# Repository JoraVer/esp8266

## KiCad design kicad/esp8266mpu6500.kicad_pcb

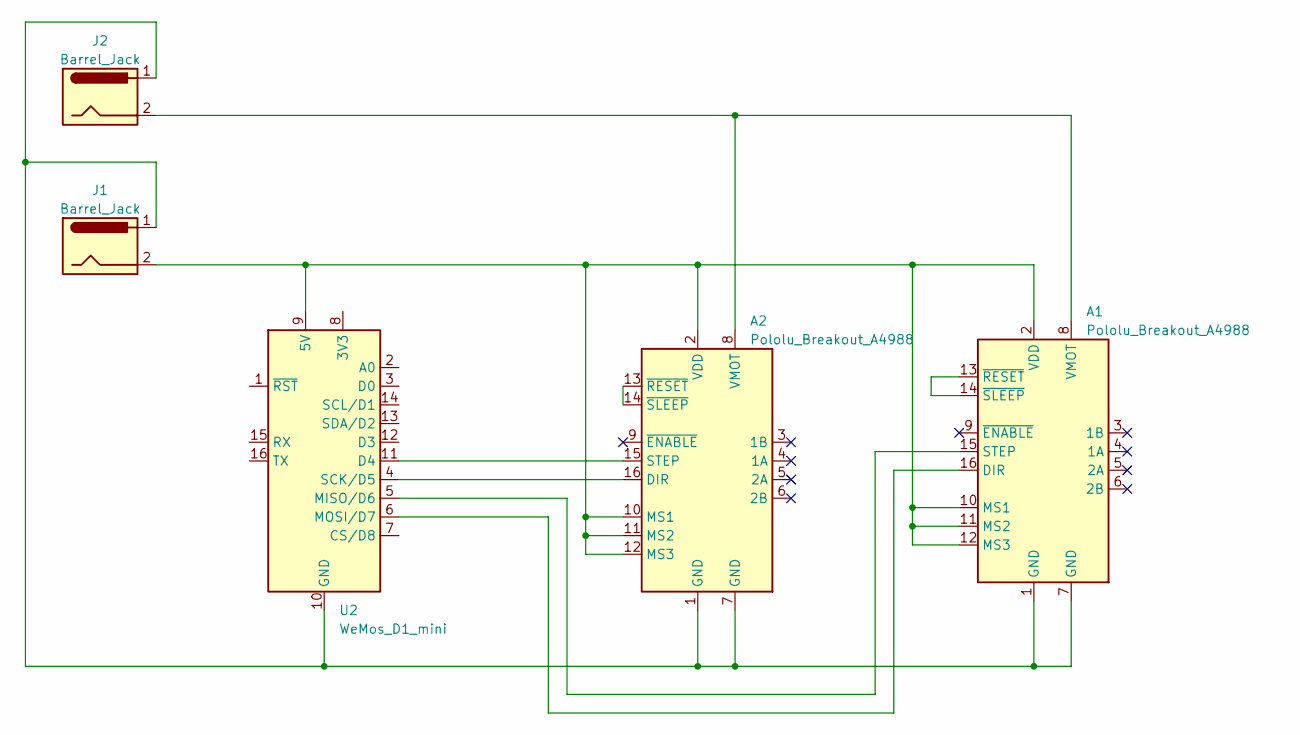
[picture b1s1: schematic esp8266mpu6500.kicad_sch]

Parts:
A1, A2: Pololu_Breakout_A4988; Pololu_Breakout-16_15.2x20.3mm
J1, J2: Barrel_Jack; BarrelJack_SwitchcraftConxall_RAPC10U_Horizontal
U2: WeMos_D1_mini; WEMOS_D1_mini_light

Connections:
unnamed: A1.16 (DIR), U2.6 (MOSI/D7)
unnamed: A1.2 (VDD), A1.10 (MS1), A1.11 (MS2), A1.12 (MS3), A2.2 (VDD), A2.10 (MS1), A2.11 (MS2), A2.12 (MS3), J1.2, U2.9 (5V)
unnamed: A1.15 (STEP), U2.5 (MISO/D6)
unnamed: A1.8 (VMOT), A2.8 (VMOT), J2.2
unnamed: A1.13 (~RESET), A1.14 (~SLEEP)
unnamed: A2.16 (DIR), U2.4 (SCK/D5)
unnamed: A2.15 (STEP), U2.11 (D4)
unnamed: A2.13 (~RESET), A2.14 (~SLEEP)
unnamed: A1.1 (GND), A1.7 (GND), A2.1 (GND), A2.7 (GND), J1.1, J2.1, U2.10 (GND)

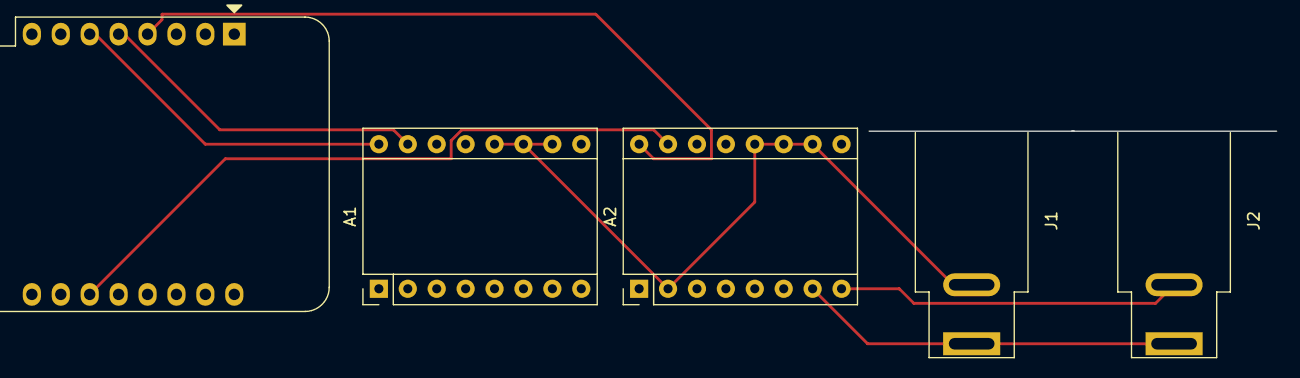
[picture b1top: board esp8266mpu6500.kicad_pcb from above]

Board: 2 copper layers, 5 parts (0 on the bottom side), 9 nets.

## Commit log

2023-03-10 First blood: Arduino proj + KiCad proj
